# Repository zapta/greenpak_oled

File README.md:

# Addressable SPI OLED display

This design demonstrates the technique of adding device addressing capabilities to a SPI bus. This provides the speed and distance of an SPI bus with the simplicity and extensibility of an I2C bus.

The addressability is achieved using a Renesas's GreenPAK SPLD devices which interprets the first byte of each SPI transaction as a meta control byte and passes the CS signal to the device only if the address encoded in the control byte matches the device's address. The supported OLED displays are 1.3" SSD1306 and SH1106. 

> **NOTE**: The SSD1306 and the SH1106 are compatible at the hardware level but require different software drivers.

Resources
* PCB schematic: https://github.com/zapta/greenpak_oled/blob/main/kicad/greenpak_oled.pdf
* GreenPAK design schematic: https://github.com/zapta/greenpak_oled/blob/main/greenpak/greenpak_oled.svg
* GreenPAK source and hex files: https://github.com/zapta/greenpak_oled/tree/main/greenpak
* Interactive BOM: https://htmlpreview.github.io/?https://github.com/zapta/greenpak_oled/blob/main/kicad/bom/ibom.html

<br>

Components side:

<br>

Display panel side:

<br>

Wiring diagram (for oled_demo.py):

## Protocol

A SPI transaction is a sequence of bytes transfer between a high-to-low and a low-to-high transitions of the ``CS`` signal. To tag a transaction with a device address, prepend to it a control byte which include the target device address as well as the desired states of the OLED ``RST`` and ``DC`` inputs.

| Bit field    | Function     | Description     |
|--------------|-------------|------------|
| Bits [7:5]   |  Reserved   | Set to 0.      |
| Bits [4:4]   |  RST        | The value of the OLED RST input. |
| Bits [3:4]   |  DC         | The value of the OLED D/C input  |
| Bits [2:1]   |  Address    | The target device address in the range [0, 7]   |

The address of each device is set by its three solder jumbers, with an open jumper
representing ``0`` and short jumper representing ``1``

## Device SPI address

The device address is set by shorting with solder the necessary solder jumpers according to this table:

|Address    | A1    | A1    | A0   |
|:--------------:|:-------------:|:------------:|:----:|
| 0   |  -   |  -    |  - |
| 1   |  -   |  -    |  Solder |
| 2   |  -   |   Solder   | -  |
| 3   |  -   |   Solder   | Solder  |
| 4   | Solder    |  -    | -  |
| 5   | Solder    |  -    |  Solder |
| 6   | Solder    |   Soler   | -  |
| 7   | Solder    |   Solder   | Solder  |

## oled_demo.py

The Python program demo_oled.py demonstrates the addressability by continuously writing a different content to each of the eight possible device addresses. Connecting one or more 
device will display on each a number that identify it's address. The demo uses a USB to SPI adapter, such as a plain Raspberry Pi Pico, that is compatible with the  Python package ``spi-adapter``.

## Timing diagrams

The screenshot below shows a typical address enabled SPI transaction. The first byte 
is the control byte ``0x12`` contains the signals ``OLED_RST=1``, ``OLED_DC=0``, and is ``ADDRESS=2``, and is matched against the device address, which happens to be 2,  and causes a match. This sets the ``OLED_RST`` and ``OLED_DC`` outputs to their respective values (no change in the case of ``OLED_RST``) and then enables ``OLED_CS`` such that the rest of the bytes are processed by the OLED device.

<br>

The following diagram zoom on the control byte. Note that the ``OLED_DC`` (and so ``OLED_RST`` when changed) stabilizes on its new level before  ``OLED_CS`` is asserted low.

<br>

## How it works?

The diagram below shows the main functional blocks of the GreenPAK design. For full details and the latest version, explore the design file ``greenpak_oled.gp6`` file using the Renesas design tool.

1. I2C programming support. Used only for flashing or reflashing the GreenPAK device and is not used in normal operation.
2. Serial to parallel shifter. A shift register that provides the four previous SPI bit values.
3. First byte detector. Generates signal that indicates the time of the 8'th bit of the control byte (the first byte in the SPI transaction)
4. Address matcher. On the last bit of the control byte, tests if the address matches.
5. OLED_CS generator. A latch that generates the the ``OLED_CS`` output signals.
6. Auxiliary signals generators. Latches for the ``OLED_RST`` and ``OLED_DC`` output signals.
  
<br>

## Making your own

To make your own Addressable SPI OLED display follow these steps:

1. Order the PCB and components.
1. Assemble the components, including the OLED panel which is soldered to the 30 pags strip.
1. Program the GreenPAK device as described below.
1. Set the display address on the SPI bus by soldering the necessary solder jumpers.

The Github repository contains an HTML interactive BOM that helps identifying the components and their values.

## Flashing the GreenPAK

Flashing the GreenPAK IC can be done in-circuit via the programming pads which are compatible with the [GreenPAK Pogo Probe](https://github.com/zapta/greenpak_pogo). The provided Python program ``flasher.py`` allows to program it using an USB to I2C adapter such as the Raspberry Pi Pico, or the Sparkfun Pro Micro RP2040. which are supported by the Python ``i2c_adapter`` package. 

## FAQ

Q: What is the operating voltage of the OLED display.

A: 3.3V nominal.

---

Q: What SPI mode is used?

A: SPI mode 0 as required by the SSD1306 and SH1106 controllers.

---

Q: What SPI speeds are supported?

A: We tested it successfully with 4Mhz SPI clock.

---

Q: Why only 3 address jumpers?

A: We run out of resources in the GreenPAK device. 

---

Q: I want to change the design of the GreenPAK device, what tools do I need?

A: The Go Configure tool is available for free from Renesas and it allows to edit and test GreenPAK designs.  https://www.renesas.com/us/en/software-tool/go-configure-software-hub

---

Q: Why GreenPAK?

A: They are inexpensive, stand alone, flexible, have a small footprint, not requiring glue components.

---

Q: What kind of a guarantee do you provide with this design?

A: None whatsoever, the design is provided 'as-is'.

---

Q: This design doesn't uses MISO. Is it possible have MISO reading with addressable SPI?

A: Yes. A MISO signal can be used without having to change the GreenPAK's design.

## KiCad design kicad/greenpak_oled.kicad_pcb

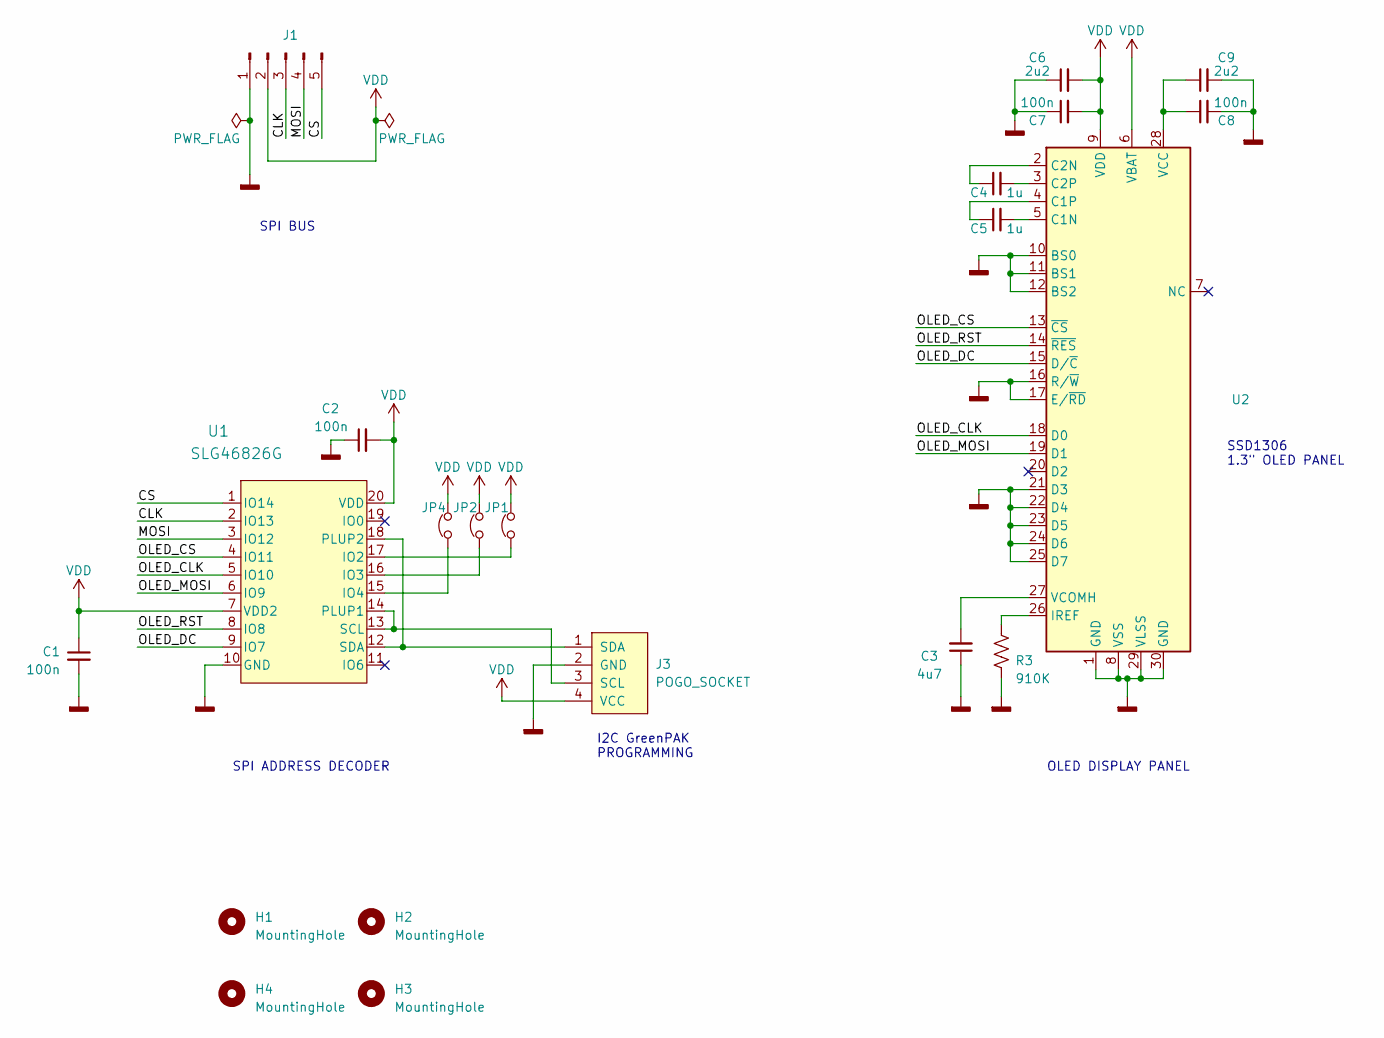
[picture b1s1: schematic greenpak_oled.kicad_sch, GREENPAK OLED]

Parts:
C1, C2, C7, C8: 100n; C_0603_1608Metric
C3: 4u7; C_0603_1608Metric
C4, C5: 1u; C_0603_1608Metric
C6, C9: 2u2; C_0603_1608Metric
H1, H2, H3, H4: MountingHole
J1: Conn_01x05_Pin; PinHeader_1x05_P2.54mm_Vertical
J3: POGO_SOCKET; GREENPAK_POGO_SOCKET
JP1, JP2, JP4: Jumper_2_Open; SolderJumper-2_P1.3mm_Open_Pad1.0x1.5mm
R3: 910K; R_0603_1608Metric
U1: SLG46826G; TSSOP20_MO-220_WECE_REN
U2: OLED-128O064D

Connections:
/CLK: J1.3, U1.2 (IO13)
/CS: J1.5, U1.1 (IO14)
/MOSI: J1.4, U1.3 (IO12)
/OLED_CLK: U1.5 (IO10), U2.18 (D0)
/OLED_CS: U1.4 (IO11), U2.13 (~CS)
/OLED_DC: U1.9 (IO7), U2.15 (D/~C)
/OLED_MOSI: U1.6 (IO9), U2.19 (D1)
/OLED_RST: U1.8 (IO8), U2.14 (~RES)
GND: C1.2, C2.1, C3.1, C6.1, C7.1, C8.2, C9.2, J1.1, J3.2 (GND), R3.2, U1.10 (GND), U2.1 (GND), U2.8 (VSS), U2.10 (BS0), U2.11 (BS1), U2.12 (BS2), U2.16 (R/~W), U2.17 (E/~RD), U2.21 (D3), U2.22 (D4), U2.23 (D5), U2.24 (D6), U2.25 (D7), U2.29 (VLSS), U2.30 (GND)
unnamed: J3.3 (SCL), U1.13 (SCL), U1.14 (PLUP1)
unnamed: J3.1 (SDA), U1.12 (SDA), U1.18 (PLUP2)
unnamed: JP1.1, U1.17 (IO2)
unnamed: JP2.1, U1.16 (IO3)
unnamed: JP4.1, U1.15 (IO4)
unnamed: C5.2, U2.5 (C1N)
unnamed: C5.1, U2.4 (C1P)
unnamed: C4.1, U2.2 (C2N)
unnamed: C4.2, U2.3 (C2P)
unnamed: R3.1, U2.26 (IREF)
unnamed: C8.1, C9.1, U2.28 (VCC)
unnamed: C3.2, U2.27 (VCOMH)
VDD: C1.1, C2.2, C6.2, C7.2, J1.2, J3.4 (VCC), JP1.2, JP2.2, JP4.2, U1.7 (VDD2), U1.20 (VDD), U2.6 (VBAT), U2.9 (VDD)

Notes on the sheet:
SSD1306 1.3" OLED PANEL
I2C GreenPAK PROGRAMMING
SPI BUS
OLED DISPLAY PANEL
SPI ADDRESS DECODER

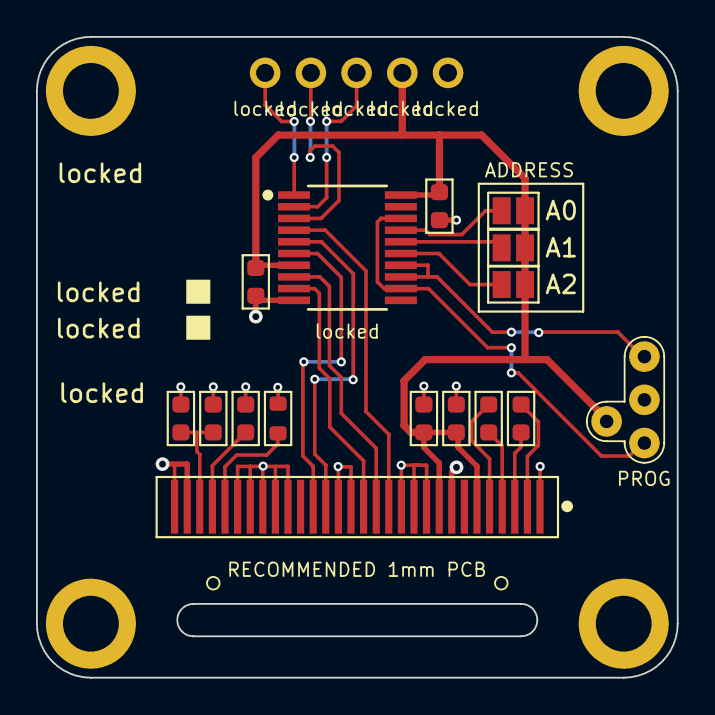
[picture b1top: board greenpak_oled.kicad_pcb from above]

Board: 2 copper layers, 35.6 x 35.6 mm, 21 parts (0 on the bottom side), 22 nets.

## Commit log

2024-01-22 Copied kicad project to the new directory.
2024-01-22 Added .gitignore and .gitattributes.
2024-01-22 Renamed left over addressable_oled to greenpak_oled.
2024-01-22 Final touched. Regenerated gerbers.
2024-01-22 Moved rest of files from greenpak_misc repository.
2024-01-22 Deleted redundant files.
2024-01-23 Renamed files to greenpak_oled.
2024-01-23 Cleaned up the oled demo.
2024-01-23 Added doc resources.
2024-01-23 Updated pcb rendering.
2024-01-23 Documentation work in progress.
2024-01-23 More progress on the documentation.
2024-01-23 Extended documentation.
2024-01-23 Extended documentation
2024-01-23 fixed typo
2024-01-23 Fixed a typo in the silkscreen
2024-01-23 Added signal capture diagram.
2024-01-23 Added timing diagram.
2024-01-23 Updated signal captures.
2024-01-23 Document now has timing diagrams.
2024-01-23 Added an annotated GreenPAK schematic.
2024-01-23 Updated the documentation.
2024-01-23 Tweaked oled demo.
2024-01-23 Changed programming pads to pogo socket.
2024-01-24 Increased the size of the POGO socket.
2024-01-24 Added a reference to the GreenPAK Pogo Probe.
2024-01-24 Tweaked the schematic to match also SH1106.
2024-01-24 Changed the PCB to have a slot instead of a cut.
2024-01-24 Tweaked the flex cable slot.
2024-01-24 Updated www pictures.
2024-01-24 Updated docs.
2024-01-24 Tweaked layout. Regenerated gerbers.
2024-01-24 Added a link to the interactive BOM.
2024-01-24 Tweaked the interactive bom comment.
2024-01-25 Simplify image links in README.md.
2024-01-25 Added white space to the doc.
2024-01-27 Removed unused schematic symbol.
2024-01-30 Added import of sh1106
2024-02-03 Added TODOs.
2024-02-05 Added wiring diagram.
2024-02-05 Integrated the wiring diagram in README.md
2024-02-05 Updated pogo socket dimensions.
2024-02-05 Updated programming socket, adjusted flex cable slot, generated gerbers 03.
2024-02-05 Updated TOdo.
